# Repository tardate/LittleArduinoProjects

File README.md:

# 869 Little Electronic Art Projects

> Latest addition :sparkles: [UART-TTL to LED Array Interface Board](./Electronics101/LED/Arrays/WS2812BControl/InterfaceBoard) - Building a simple interface board for connecting a CH340-based UART-TTL adapter to an WS2811 or WS2812B LED strip.

LEAP is just my personal collection of electronics projects - usually involving an Arduino or other microprocessor in one way or another.
Some are full-blown projects, while many are trivial breadboard experiments, intended to learn and explore something interesting.

Projects are often inspired by things found wild on the net,
or ideas from the many great [electronics podcasts and YouTube channels](./notebook/).
Feel free to borrow liberally, and if you spot any issues do let me know (or send a PR!).
See the individual projects for credits where due.

For a while I have also included various scale modelling projects here too,
but I've now split those off into a new repository.
Check out
[LittleModelArt](https://modelart.tardate.com/)
if you are looking for the modelling projects!

## The LEAP Project Index

The best way to browse the projects is to take a look at the
[LEAP Catalog](https://leap.tardate.com/).
It's actually a static web site generated directly from the repository. Try it out:

## Getting Up and Running

Some projects require additional libraries including FastLED, FlexiTimer2, RadioHead.
A set of such libraries are included as submodules of this repository,
see the [libraries/](./libraries) page for more information on the included libraries and submodule management.

For Arduino projects, I have the Arduino IDE sketchbook location (in preferences) set to the root of this repository.
This makes all the projects available to me in the IDE, and automatically includes libraries
that are linked as git submodules in the [libraries/](./libraries) folder.

If you don't have the Arduino IDE setup this way, libraries can be retrieved with git,
or you can just install them separately as you would any other library.

If you clone this repo, also update the submodules to have them available for compilation:

    git submodule update --init

To pull submodule updates later on:

    git submodule foreach git pull

To update a specific library later on, e.g. `TextFinder`:

    git submodule update --remote libraries/TextFinder

## The 10th Anniversary Archive

I started the
[LittleArduinoProjects](https://github.com/tardate/LittleArduinoProjects)
GitHub repository back in 2014.
Over the years it accumulated over 2Gb of obsolete commits, and so much git history that it wasn't even possible
to do a `git push` of the entire repo without resorting to [batch tricks](https://stackoverflow.com/questions/15125862/github-remote-push-pack-size-exceeded).

Entering the 11th year of the repository, I decided to do a one-time squash of the project history and essentially restart the git history from scratch:

* <https://github.com/tardate/LittleArduinoProjects> remains the primary repo
    * but with the git history squashed
        * retains the original first commit as the base, so any clones and forks will share a common root commit
    * I've taken the opportunity to rename the working branch from `master` to `main`
* <https://github.com/tardate/LittleArduinoProjects-archive-2014-2024> is a snapshot of the repository prior to the squash
    * marked as `archived` in GitHub, with issues etc disabled
    * retains the full git history in the very unlikely event that anyone needs to refer back to specific change

What this means in practice:

* if you are just viewing LittleArduinoProjects on [GitHub](https://github.com/tardate/LittleArduinoProjects) or the [web](https://leap.tardate.com/), there is no impact
* if you have a clone of the LittleArduinoProjects repository:
    * the simplest is just to throw it away and make a fresh clone of the repo
    * if you have work-in-progress changes on private branches, you will probably want to cherry-pick the changes to a branch based on the new `main` branch
        * if you need help with that, reach out or post an issue
* old pull requests (PR) will be based on the old history. Reviving any old PRs will require the changes to be rebased on the new history.

Hopefully this will help make the LittleArduinoProjects repository fit for use for another 10 years or more..

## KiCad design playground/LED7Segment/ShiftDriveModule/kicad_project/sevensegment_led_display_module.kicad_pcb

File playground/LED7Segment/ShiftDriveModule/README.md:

# #178 7-Segment Shift Drive Module

A custom 7-segment LED display module PCB with 74HC595 shift register interface.

Here's a quick video of the module in action:

## Notes

This is my version of project 2 from the
[KiCad like a Pro](http://txplore.tv/courses/kicad-pro)
course from Tech Explorations.

It is essentially the [LEAP#177 7-Segment Shift Drive](../ShiftDrive) project but as a custom PCB.
The PCB includes a single 7-Segment LED, current limiting resistors and 74HC595 shift register.

The PCB design was done with [KiCad](http://kicad-pcb.org/).

I sent these off for production at [OSH Park](https://oshpark.com/shared_projects/gs9XjBpw), and they arrived (in Singapore) a month later (Jan 17th -> Feb 17th). They turned out quite well, certainly no issues with the fab.

After examining the PCBs, I found a few things that could be improved in the design:

* doh! I got the data/latch labels around the wrong way (fixed in 1.1.0)
* pin header label was obscured by R1 (fixed in 1.1.0)
* the thru-hole pads for the resistors are super-chunky compared to the other component holes. Not a real issue - just looks weird.
* orientation of the 74HC595 should probably be a clearer (like a notch in the footprint outline)

But they work just fine!

### Register-Pin Mapping

Here's a summary of how the bits in the shift register are mapped to LED segments:

| Bit | Segment                    |
|-----|----------------------------|
|  0  |  A - top horizontal        |
|  1  |  B - top right vertical    |
|  2  |  C - bottom right vertical |
|  3  |  D - bottom horizontal     |
|  4  |  E - bottom left vertical  |
|  5  |  F - top left vertical     |
|  6  |  G - center  horizontal    |
|  7  |  dp - decimal point        |

### Test Script

The [ShiftDriveModule.ino](./ShiftDriveModule.ino) sketch drives the module with a simple counter from 0-9, with the decimal point lit for even numbers.

The script manipulates the data/latch/clock output directly (no SPI), and assumes the following pin connections:

| Arduino Pin | Module Pin |
|-------------|------------|
| 5V          | Vcc        |
| GND         | GND        |
| 3           | DATA       |
| 4           | LATCH      |
| 5           | CLOCK      |

## Construction

See the [KiCad project](./kicad_project/sevensegment_led_display_module.pro) for all the details. Here's the result:

Here are the finished boards. For the one I've already soldered I first used male pins (to plug-in to a breadboard),
but if I do another I'll probably use female pin headers instead.

## Credits and References

* [This ShiftDriveModule project on OSH Park](https://oshpark.com/shared_projects/gs9XjBpw)
* [LEAP#177 7-Segment Shift Drive](../ShiftDrive) - breadboard version of the circuit
* [KiCad like a Pro](http://txplore.tv/courses/kicad-pro) - course materials
* [KiCad](http://kicad-pcb.org/)
* [gerblook](http://gerblook.org/) - nice tool for testing a set of gerber files
* [OSH Park](https://oshpark.com/)
* [HARDWARE HANGOUT with James "Laen" Neal from OSH Park!](https://www.youtube.com/watch?v=XssjD97-xGM) - where I first learned of OSH Park
* [..as mentioned on my blog](https://blog.tardate.com/2016/02/littlearduinoprojects178-making-7.html)

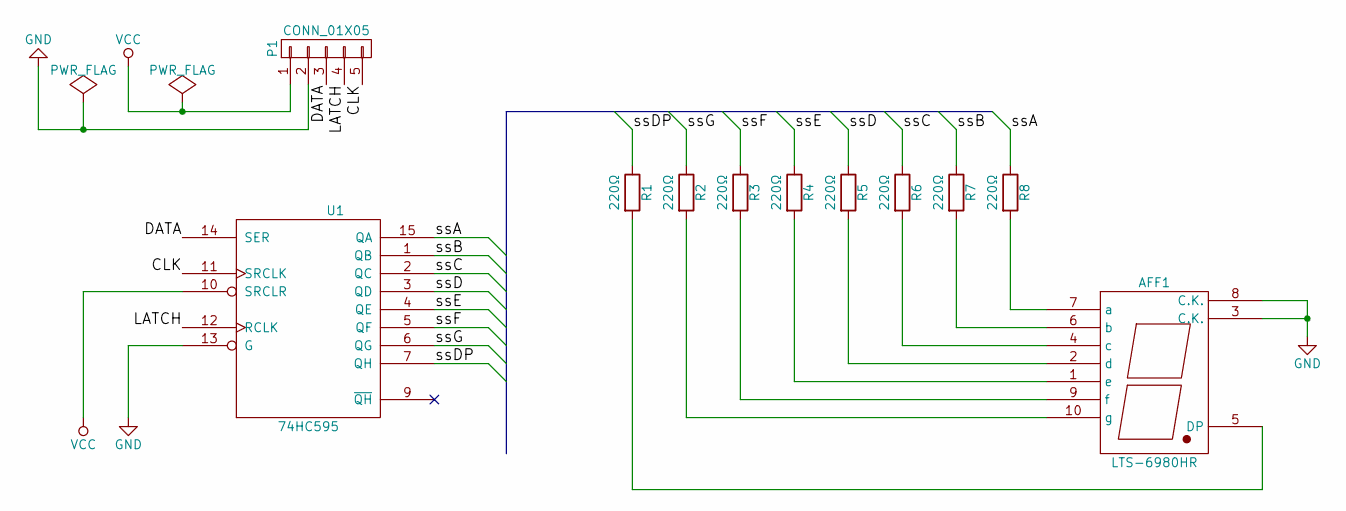
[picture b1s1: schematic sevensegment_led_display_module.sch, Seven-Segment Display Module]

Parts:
AFF1: LTS-6980HR; 7SegmentLED_LTS6760_LTS6780
P1: CONN_01X05; Pin_Header_Straight_1x05
R1, R2, R3, R4, R5, R6, R7, R8: 220Ω; Resistor_Horizontal_RM10mm
U1: 74HC595; DIP-16_W7.62mm

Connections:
/CLK: P1.5, U1.11 (SRCLK)
/DATA: P1.3, U1.14 (SER)
/LATCH: P1.4, U1.12 (RCLK)
/ssA: R8.1, U1.15 (QA)
/ssB: R7.1, U1.1 (QB)
/ssC: R6.1, U1.2 (QC)
/ssD: R5.1, U1.3 (QD)
/ssDP: R1.1, U1.7 (QH)
/ssE: R4.1, U1.4 (QE)
/ssF: R3.1, U1.5 (QF)
/ssG: R2.1, U1.6 (QG)
GND: AFF1.3 (C.K.), AFF1.8 (C.K.), P1.2, U1.8 (GND), U1.13 (G)
unnamed: AFF1.1 (e), R4.2
unnamed: AFF1.2 (d), R5.2
unnamed: AFF1.4 (c), R6.2
unnamed: AFF1.5 (DP), R1.2
unnamed: AFF1.6 (b), R7.2
unnamed: AFF1.7 (a), R8.2
unnamed: AFF1.9 (f), R3.2
unnamed: AFF1.10 (g), R2.2
VCC: P1.1, U1.10 (SRCLR), U1.16 (VCC)

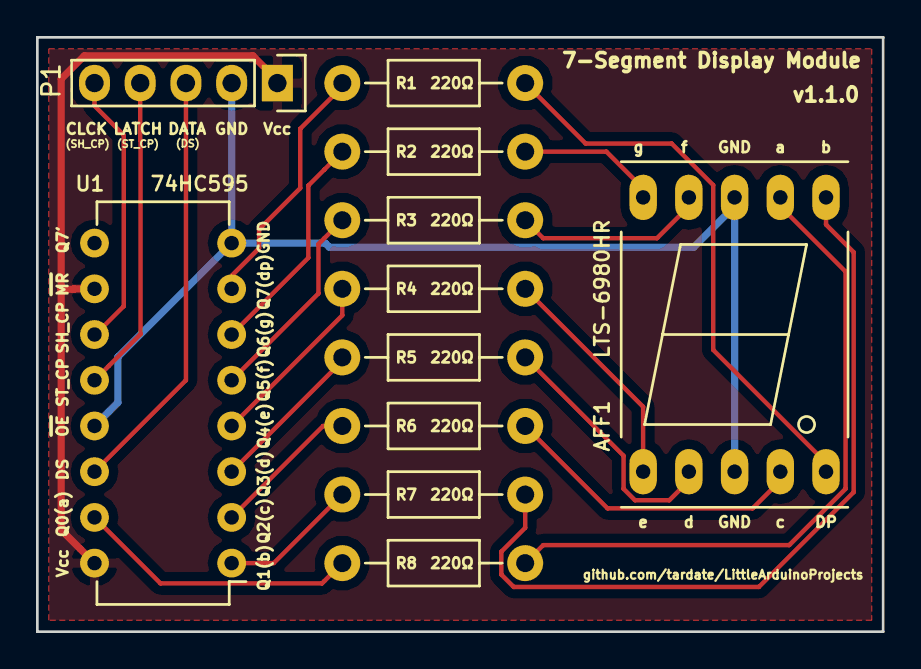
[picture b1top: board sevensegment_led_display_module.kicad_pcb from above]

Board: 2 copper layers, 47.0 x 33.0 mm, 11 parts (0 on the bottom side), 21 nets.

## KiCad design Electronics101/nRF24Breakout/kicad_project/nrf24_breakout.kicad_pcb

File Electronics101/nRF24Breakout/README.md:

# #176 nRF24Breakout

A simple PCB breadboard adapter for 8-pin nRF24 modules

## Notes

This is my version of project 1 from the
[KiCad like a Pro](http://txplore.tv/courses/kicad-pro)
course from Tech Explorations.

It's about as simple as it gets - my main objective here is to try out the process
of sending PCB design to a small-quantity production fab.
I got interested in doing this after [seeing this hangout](https://www.youtube.com/watch?v=XssjD97-xGM) with the
founder of OSH Park.

The PCB design was done with [KiCad](http://kicad-pcb.org/).

I sent these off for production at [OSH Park](https://oshpark.com/shared_projects/Js6JrEyC), and they arrived (in Singapore) a month later (Jan 17th -> Feb 17th). They turned out quite well, certainly no issues with the fab. I'll be using these for some nRF24 projects.

After examining the PCBs, I can see a few things that could be improved in the design:

* the font size I used for pin labelling is just barely large enough to read
* I didn't allow space between the 2x4 pin header and the pin labels (with the pin adapter installed, the labels are partially obscured)
* the board size does not match the nRF24 unit very well (the module overlaps the edge of the board). I think the module might be better rotated 90˚.

See [nRF24/PingPong](../../playground/nRF24/PingPong), my first shot at using the adapters for real. They worked great!

## Construction

See the [KiCad project](./kicad_project/nrf24_breakout.pro) for all the details. Here's the result:

## Credits and References

* [KiCad like a Pro](http://txplore.tv/courses/kicad-pro) - course materials
* [This nRF24Breakout project on OSH Park](https://oshpark.com/shared_projects/Js6JrEyC)
* [KiCad](http://kicad-pcb.org/)
* [gerblook](http://gerblook.org/) - nice tool for testing a set of gerber files
* [OSH Park](https://oshpark.com/)
* [HARDWARE HANGOUT with James "Laen" Neal from OSH Park!](https://www.youtube.com/watch?v=XssjD97-xGM) - where I first learned of OSH Park
* [..as mentioned on my blog](https://blog.tardate.com/2016/02/littlearduinoprojects176-nrf24-breakout.html)

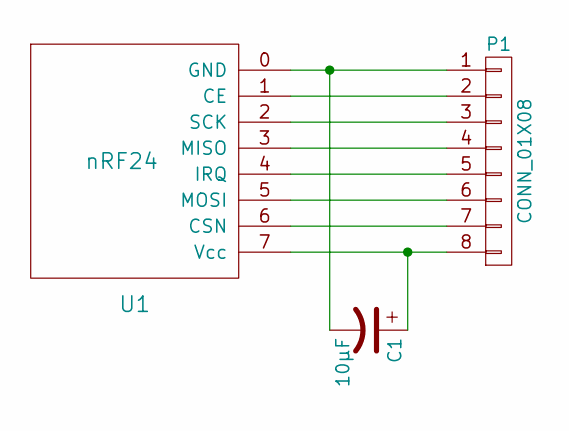
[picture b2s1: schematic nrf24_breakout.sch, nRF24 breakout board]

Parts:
C1: 10µF; C_Radial_D6.3_L11.2_P2.5
P1: CONN_01X08; Pin_Header_Straight_1x08
U1: nRF24

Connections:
unnamed: C1.1, P1.8, U1.7 (Vcc)
unnamed: C1.2, P1.1, U1.0 (GND)
unnamed: P1.2, U1.1 (CE)
unnamed: P1.3, U1.2 (SCK)
unnamed: P1.4, U1.3 (MISO)
unnamed: P1.5, U1.4 (IRQ)
unnamed: P1.6, U1.5 (MOSI)
unnamed: P1.7, U1.6 (CSN)

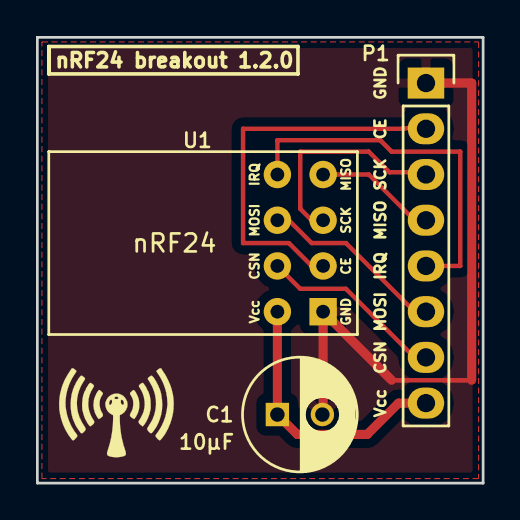
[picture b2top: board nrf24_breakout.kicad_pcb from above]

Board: 2 copper layers, 24.8 x 24.8 mm, 3 parts (0 on the bottom side), 8 nets.

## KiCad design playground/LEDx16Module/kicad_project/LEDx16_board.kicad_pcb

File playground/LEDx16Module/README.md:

# #179 LEDx16Module

A custom 16 LED SMD PCB with 74HC595 shift register interface.

Here's a quick video of the module running the demo code:

## Notes

This is my version of project 3 from the
[KiCad like a Pro](http://txplore.tv/courses/kicad-pro)
course from Tech Explorations.

The board exposes a dual 74HC595 shift register interface for microcontroller control
of an array of 16 LEDs with current-limiting resistors.

The PCB design was done with [KiCad](http://kicad-pcb.org/).

I haven't sent the boards for production yet - first sourcing and verifying the SMD components.
When I've built and tested the board, I'll update and share the OSH Park project and Arduino code.

I sent these off for production at [OSH Park](https://oshpark.com/shared_projects/E2aHiqP5), and they turned out quite well.
I think I could have picked a footprint for the SOP16 ships with longer pads to make them easier to solder by hand.

One variation I've made in the circuit from the KiCad like a Pro course:
I've explicitly grounded pin 13 (output enable - active low).
If left floating, I've found the circuit to be unreliable depending on power conditions (output enable floats high).

## Construction

See the [KiCad project](./kicad_project/LEDx16Module.pro) for all the details. Here's the result:

### Example Parts Sources on Aliexpress

* [74HC595 SOP16](https://www.aliexpress.com/item/Free-shipping-100pcs-74HC595D-74HC595-SOP16/905837111.html)
* [220Ω 0805](https://www.aliexpress.com/item/0805-SMD-Resistors-220R-220-ohm-1-8W-5-0805-SMD-Resistors-0805-Chip-resistor-500pcs/851490480.html)
* [220µF 16V 6x7mm SMD](https://www.aliexpress.com/item/Free-shiping-10pcs-16V-220UF-SMD-6x7mm-chip-Aluminum-Electrolytic-Capacitor/1173598774.html)
* [0805 LEDs (5 colours)](https://www.aliexpress.com/item/Free-Shipping-100PCS-0805-Ultra-Bright-SMD-R-G-B-W-Y-LEDs-yellow-blue-White/859788444.html)

## Demo

The [LEDx16Module.ino](./LEDx16Module.ino) sketch runs a simple demo sequence on the board from an Arduino using hardware SPI.

## Credits and References

* [KiCad like a Pro](http://txplore.tv/courses/kicad-pro) - course materials
* [KiCad](http://kicad-pcb.org/)
* [gerblook](http://gerblook.org/) - nice tool for testing a set of gerber files
* [OSH Park](https://oshpark.com/)
* [HARDWARE HANGOUT with James "Laen" Neal from OSH Park!](https://www.youtube.com/watch?v=XssjD97-xGM) - where I first learned of OSH Park

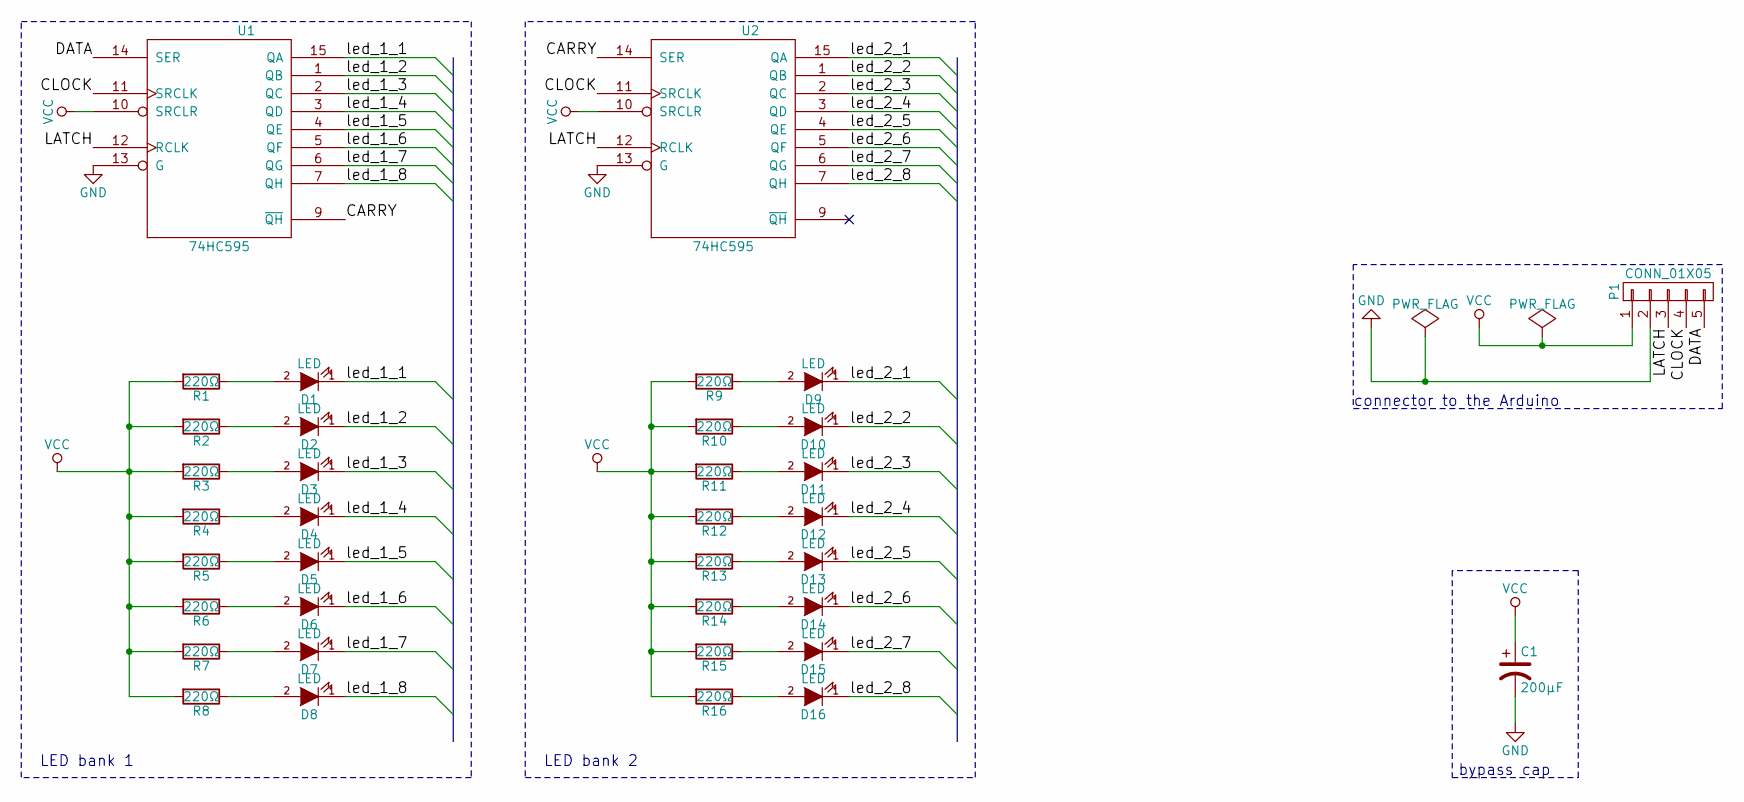
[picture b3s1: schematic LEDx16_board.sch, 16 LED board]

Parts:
C1: 200µF; c_elec_6.3x5.3
D1, D2, D3, D4, D5, D6, D7, D8, D9, D10, D11, D12, D13, D14, D15, D16: LED; LED_0805
P1: CONN_01X05; Pin_Header_Straight_1x05
R1, R2, R3, R4, R5, R6, R7, R8, R9, R10, R11, R12, R13, R14, R15, R16: 220Ω; R_0805_HandSoldering
U1, U2: 74HC595; SO-16-N

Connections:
/CARRY: U1.9 (~QH), U2.14 (SER)
/CLOCK: P1.4, U1.11 (SRCLK), U2.11 (SRCLK)
/DATA: P1.5, U1.14 (SER)
/LATCH: P1.3, U1.12 (RCLK), U2.12 (RCLK)
/led_1_1: D1.1 (K), U1.15 (QA)
/led_1_2: D2.1 (K), U1.1 (QB)
/led_1_3: D3.1 (K), U1.2 (QC)
/led_1_4: D4.1 (K), U1.3 (QD)
/led_1_5: D5.1 (K), U1.4 (QE)
/led_1_6: D6.1 (K), U1.5 (QF)
/led_1_7: D7.1 (K), U1.6 (QG)
/led_1_8: D8.1 (K), U1.7 (QH)
/led_2_1: D9.1 (K), U2.15 (QA)
/led_2_2: D10.1 (K), U2.1 (QB)
/led_2_3: D11.1 (K), U2.2 (QC)
/led_2_4: D12.1 (K), U2.3 (QD)
/led_2_5: D13.1 (K), U2.4 (QE)
/led_2_6: D14.1 (K), U2.5 (QF)
/led_2_7: D15.1 (K), U2.6 (QG)
/led_2_8: D16.1 (K), U2.7 (QH)
GND: C1.2, P1.2, U1.8 (GND), U1.13 (G), U2.8 (GND), U2.13 (G)
unnamed: D1.2 (A), R1.1
unnamed: D2.2 (A), R2.1
unnamed: D3.2 (A), R3.1
unnamed: D4.2 (A), R4.1
unnamed: D5.2 (A), R5.1
unnamed: D6.2 (A), R6.1
unnamed: D7.2 (A), R7.1
unnamed: D8.2 (A), R8.1
unnamed: D9.2 (A), R9.1
unnamed: D10.2 (A), R10.1
unnamed: D11.2 (A), R11.1
unnamed: D12.2 (A), R12.1
unnamed: D13.2 (A), R13.1
unnamed: D14.2 (A), R14.1
unnamed: D15.2 (A), R15.1
unnamed: D16.2 (A), R16.1
VCC: C1.1, P1.1, R1.2, R2.2, R3.2, R4.2, R5.2, R6.2, R7.2, R8.2, R9.2, R10.2, R11.2, R12.2, R13.2, R14.2, R15.2, R16.2, U1.10 (SRCLR), U1.16 (VCC), U2.10 (SRCLR), U2.16 (VCC)

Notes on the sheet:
connector to the Arduino
bypass cap
LED bank 2
LED bank 1

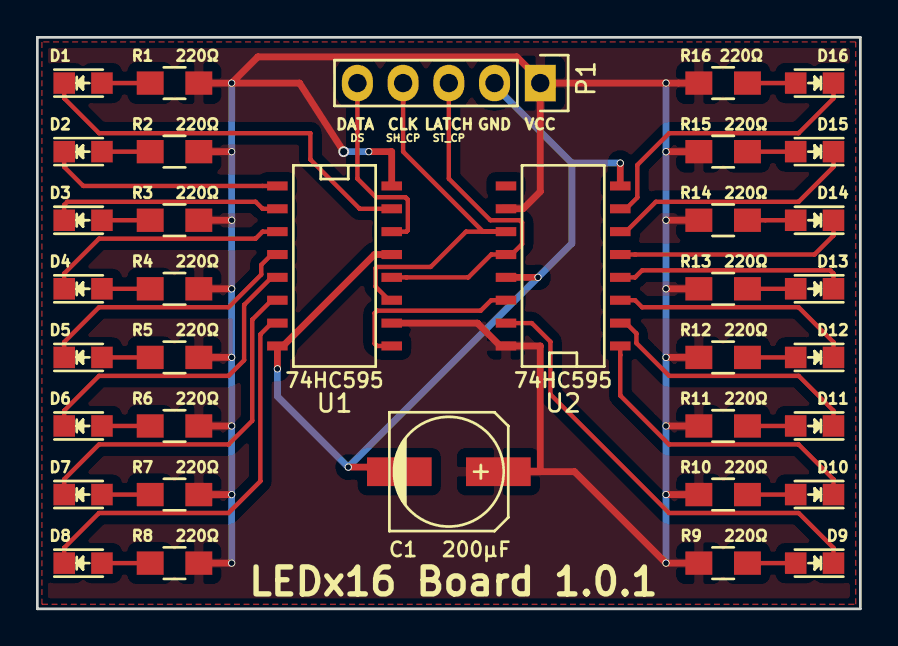
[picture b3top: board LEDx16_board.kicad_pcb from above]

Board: 2 copper layers, 45.7 x 31.8 mm, 36 parts (0 on the bottom side), 38 nets.

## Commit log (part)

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2025-12-03 add to catalog
2025-12-03 [LM339/InvertingComparator] add project (#258)
    * [LM339/InvertingComparator] add project
    * add to catalog
2025-12-07 [CD4029/Counter] add project
2025-12-07 [CD4029/Counter] add project (#259)
    * [CD4029/Counter] add project
    * add to catalog
2025-12-12 [OpticalSensors/3DU5C] add project
2025-12-12 add note on PT334-6C parts
2025-12-12 add CHANZON IR specs
2025-12-12 [OpticalSensors/3DU5C] add project (#260)
    * [OpticalSensors/3DU5C] add project
    * add to catalog
    * add note on PT334-6C parts
    * update catalog
    * add CHANZON IR specs
    * update catalog
2025-12-14 [IR/fc-51-sensor-module] add project
2025-12-14 [IR/fc-51-sensor-module] add project (#261)
    * [IR/fc-51-sensor-module] add project
    * add to catalog
2025-12-14 [LM393/SquareWaveOscillator] add project
2025-12-31 update default ruby to 3.3.6 for jekyll
2025-12-31 update default ruby to 3.3.6 for jekyll (#263)
2025-12-31 rm Gemfile.lock
2025-12-31 ignore Gemfile.lock
2025-12-31 ignore Gemfile.lock (#264)
    * rm Gemfile.lock
    * ignore Gemfile.lock
2025-12-31 [SMDPracticeBoards/BasicKit1] split out as a separate project
2026-01-01 [SMDPracticeBoards/LedMatrixKit1] add project
2026-01-01 update notes
2026-01-01 [SMDPracticeBoards/LedMatrixKit1] add project (#265)
    * [SMDPracticeBoards/BasicKit1] split out as a separate project
    * [SMDPracticeBoards/RingCounterKit1] split out as a separate project
    * [SMDPracticeBoards/LedMatrixKit1] add project
    * add to catalog
    * update notes
2026-01-02 Fix: catalog settings should be configured in html
2026-01-02 update repo branch ref
2026-01-04 [ESP8266/micropython/wifiTempSensor] add project
2026-01-04 [ESP8266/micropython/esp-01-temperature-logger] add project (#267)
    * [ESP8266/micropython/wifiTempSensor] add project
    * update notes
2026-01-06 [ESP8266/micropython/esp-12-temperature-logger] tidy notes
2026-01-06 [ESP8266/micropython/esp-12-temperature-logger] tidy notes (#268)
2026-01-06 update CD to ruby 3.3.10, Node 22.x and, Ubuntu Noble 24.04 (#269)
2026-01-06 tidy notes
2026-01-06 final data
2026-01-06 [ESP8266/micropython/esp-12-temperature-logger] add project (#270)
    * [ESP8266/micropython/esp-12-temperature-logger] add project
    * add to catalog
    * tidy notes
    * update notes
    * final data
2026-01-07 [esp-12-temperature-logger] fix token refresh
2026-01-07 [esp-12-temperature-logger] fix token refresh (#271)
2026-01-08 [esp-12-temperature-logger] update stats, dashboard, and more robust code
2026-01-12 [esp-12-temperature-logger] Fix: sampling should allow for ubidots STEM account limits
2026-01-12 [esp-12-temperature-logger] Fix: sampling should allow for ubidots STEM account limits (#274)
2026-01-12 [PiPico/About] add project
2026-01-12 [PiPico/About] add project (#275)
    * [PiPico/About] add project
    * add to catalog
2026-01-13 [PiPico2/About] add project
2026-01-13 update assets for BidirectionalLevelShifter
2026-01-13 [PiPico2/About] add project (#276)
    * [PiPico2/About] add project
    * add to catalog
    * update assets
    * update assets for BidirectionalLevelShifter
2026-01-13 update DHT11 references
2026-01-13 [playground/DHT11/Tester] add project
2026-01-13 update DHT-Sensor-Library
2026-01-13 [playground/DHT11/UnifiedSensorTest] add project
2026-01-13 update xrefs
2026-01-13 [playground/DHT11/Tester] add project (#277)
    * update DHT11 references
    * [playground/DHT11/Tester] add project
    * add to catalog
    * update DHT-Sensor-Library
    * update libraries/Adafruit_Sensor
    * [playground/DHT11/UnifiedSensorTest] add project
2026-01-13 [playground/DHT21/Tester] add project
2026-01-13 [playground/DHT21/Tester] add project (#278)
    * [playground/DHT21/Tester] add project
    * add to catalog
2026-01-16 [CHA81Kit] add project
2026-01-16 Tidy Fritzing Parts and project details
2026-01-16 Tidy Fritzing Parts and project details (#280)
2026-01-18 tidy CD4511-related projects
2026-01-19 [74LS161/BcdCounter] add project
2026-01-19 [74LS47/FullCycle] add project
2026-01-20 [Equipment/HandheldSolderingIrons] tidy notes
2026-01-20 update current prod ref
2026-01-20 [Equipment/HandheldSolderingIrons] tidy notes (#282)
    * [Equipment/HandheldSolderingIrons] tidy notes
    * update current prod ref
2026-01-20 [SwitchModePowerSupplies] tidy notes
2026-01-21 [XL4015Module1] add project
2026-01-21 update categories
2026-01-21 [XL4015Module2] add project (#283)
    * [SwitchModePowerSupplies] tidy notes
    * [XL4015Module1] add project
    * update naming
    * update categories
2026-01-21 [BuckConverterModules] update hero image
2026-01-21 [BuckConverterModules] update hero image (#284)
2026-01-22 [AdjustablePowerSupplyKit] update notes
2026-01-22 [AdjustablePowerSupplyKit] update notes (#285)
2026-01-23 [playground/DHT21/Tester] update with new device (#286)
2026-01-23 [BidirectionalLevelShifter/Modules] add 4-channel module tests
2026-01-23 [BidirectionalLevelShifter/Modules] add 4-channel module tests (#287)
    * [BidirectionalLevelShifter/Modules] add 4-channel module tests
    * tidy notes
2026-01-26 switch to ruby 3.4.3 for jekyll build
2026-01-26 switch to ruby 3.4.3 for jekyll build (#288)
2026-01-29 switch to ruby 3.4.8 to fix build cache issue (#289)
2026-01-30 [BMP280/Module] add project
2026-01-30 update schematics
2026-01-30 update images and purchase refs - OLED
2026-01-30 [BMP280/Module] add project (#290)
    * [BMP280/Module] add project
    * add to catalog
    * update schematics
    * update catalog
    * update images and purchase refs - OLED
2026-01-30 [HamClock] update (#291)
2026-01-30 [BMP180/Module] add project
2026-01-30 xref projects
2026-01-30 [BMP180/Module] add project (#292)
    * [BMP180/Module] add project
    * add to catalog
    * xref projects
2026-02-02 [Power/220VInverter] add project
2026-02-02 [Power/220VInverter] add project (#293)
    * [Power/220VInverter] add project
    * add to catalog
2026-02-03 update catalog/categorisation
2026-02-03 [Power/220VInverter] tidy notes (#294)
    * [Power/220VInverter] tidy notes
    * update catalog/categorisation
2026-02-03 [Power/220vBoostConverterModule] mv folder and add isolation notes
2026-02-03 [Power/220vBoostConverterModule] mv folder and add isolation notes (#295)
2026-02-05 [PIC] refresh and tidy notes, images, and links
2026-02-06 [PIC/PIC16F84ABlinky] update with mplab x 6.20/6.30
2026-02-06 [PIC/GettingBlinky/UsingC] update with mplab x 6.20/6.30
2026-02-06 update pic categories
2026-02-06 [PIC] update projects with MPLAB X IDE 6.20 (#296)
    * [PIC] refresh and tidy notes, images, and links
    * [PIC/GettingBlinky] update with mplab x 6.20
    * [PIC/PIC16F84ABlinky] update with mplab x 6.20/6.30
    * [PIC/GettingBlinky/UsingC] update with mplab x 6.20/6.30
    * update catalog
    * update pic categories
2026-02-09 [BME280/Modules] add projects
2026-02-09 [BME280/Module3V] update schematic
2026-02-10 [HamClock] update project with BME280 and HamClock news
2026-02-10 [DIYHamClockHat] add project
2026-02-10 [HamClock] update project with BME280 and HamClock news (#298)
    * [BME280/Module3V] update schematic
    * [HamClock] update project with BME280 and HamClock news
    * [DIYHamClockHat] add project
    * add to catalog
2026-02-10 [RaspberryPi/i2c] add project
2026-02-10 [RaspberryPi/i2c] add project (#299)
    * [RaspberryPi/i2c] add project
    * add to catalog
2026-02-13 [playground/LED8x8] update existing projects
2026-02-13 [playground/RotaryEncoderModule] update code
2026-02-13 [ShiftDriveModule] tidy notes
2026-02-14 [playground/move-nums] add project
2026-02-14 [LED8x8Module] tidy notes
2026-02-14 [playground/move-nums] Fix: moveNums refs
2026-02-14 [playground/move-nums] Fix: moveNums refs (#301)
2026-02-23 Fix: catalogs should wrap long titles and tag lists
2026-02-23 Fix: catalogs should wrap long titles and tag lists (#302)
2026-02-24 [001-010] review projects
2026-02-24 [001-010] review & tidy projects (#303)
    * [001-010] review projects
    * update catalog
    * update CD4026 refs
2026-02-25 [arduino-cookbook] update refs
2026-02-25 [arduino-cookbook] update refs (#304)
2026-02-27 [BoostBuckConverterModule] update build and notes
2026-02-27 [xToolS1] add recommended settings
2026-02-27 [BoostBuckConverterModule] update build and notes (#305)
    * [BoostBuckConverterModule] update build and notes
    * update catalog
    * [xToolS1] add recommended settings
    * tidy notes
2026-02-27 [PIC] udpate PICkit 3 on macOS notes (#306)
    * [PIC] udpate PICkit 3 on macOS notes
    * update catalog
    * update catalog
2026-03-02 [CD4028/QuadExclusiveInterlock] add project
2026-03-02 update schematic
2026-03-02 [CD4028/QuadExclusiveInterlock] add project (#307)
    * [CD4028/QuadExclusiveInterlock] add project
    * add to catalog
    * update catalog
    * update schematic
2026-03-04 [NLB/BambuLabP1S] add notes
2026-03-04 [NLB/FlashforgeCreatorPro2] update notes
2026-03-04 [NLB/FlashforgeCreatorPro2] update notes (#309)
2026-04-09 [Radio/HamClock/OHB] add project
2026-04-09 tidy
2026-04-09 [Radio/HamClock/OHB] add project (#310)
    * [Radio/HamClock/OHB] add project
    * add to catalog
    * tidy
2026-04-20 add hero image
2026-04-20 [LedDrivers/YLD8-12X1W] add notes (#311)
    * [LedDrivers/YLD8-12X1W] add notes
    * add to catalog
    * add hero image
2026-04-22 [NandLogic/AND] add project
2026-04-22 [NandLogic/OR] add project
2026-04-22 [NandLogic/NOR] add project
2026-04-22 [NandLogic/NOT] add project
2026-04-22 [NandLogic/XNOR] add project
2026-04-22 xref nand logic projects
2026-04-22 [NandLogic/MUX] add project
2026-04-22 [NandLogic/DEMUX] add project
2026-04-22 [NandLogic] add projects (#312)
    * [NandLogic/AND] add project
    * [NandLogic/OR] add project
    * [NandLogic/NOR] add project
    * [NandLogic/NOT] add project
    * [NandLogic/XOR] add project
    * [NandLogic/XNOR] add project
2026-04-29 Fix: book covers should be limited in image size (#313)
2026-05-05 [555Timer/ML555] add project
2026-05-05 [555Timer/ML555] add project (#314)
    * [555Timer/ML555] add project
    * add to catalog
    * tidy notes
2026-06-03 [OpticalSensors] add refs
2026-06-03 [OpticalSensors] add refs (#315)
2026-06-09 [ATtiny/TotalSleep] update project notes
2026-06-09 [ATtiny] update images
2026-06-09 update categorisation
2026-06-09 [AvrHardwarePWM] update catalog entry
2026-06-09 [ATtiny] tidy and update projects (#316)
    * [ATtiny] tidy and update projects
    * [ATtiny/TotalSleep] update project notes
    * [ATtiny] update images
    * update catalog
    * update categorisation
    * [AvrHardwarePWM] update catalog entry
2026-06-09 [TM1638] update code
2026-06-13 [playground/2d6] add project
2026-06-13 fix step-up converter categorisation
2026-06-13 [playground/2d6] add project (#317)
    * tidy LED7Segment project notes
    * [TM1638] update code
    * [playground/2d6] add project
    * add to catalog
    * fix step-up converter categorisation
2026-06-17 [the-art-of-electronics] add references
2026-06-17 [electronic-principles] add refs
2026-06-17 [Switches/MomentaryDPDT] add project
2026-06-17 [Switches/MomentaryDPDT] add project (#319)
    * [Switches/MomentaryDPDT] add project
    * add to catalog
2026-06-23 [catalog] update script
2026-06-23 [catalog] update script (#320)
2026-06-24 [catalog] update template.fzz
2026-06-24 update project notes
2026-06-24 update catalog entries
2026-06-24 update hero image
2026-06-24 [UltrasonicLevitatorKit] add project (#321)
    * [catalog] update template.fzz
    * [UltrasonicLevitatorKit] add project
    * update project notes
    * add to catalog
    * update catalog entries
    * update hero image
2026-06-24 fix: V-002 security vulnerability
    Automated security fix generated by OrbisAI Security
2026-06-24 fix: add buffer-length check in display_controller.cpp
    The display_controller
2026-06-24 update formatting
2026-06-24 [AT89C2051/Blinky] update sdcc (#323)
    * [AT89C2051/Blinky] update sdcc
    * update formatting
